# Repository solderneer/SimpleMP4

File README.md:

# SimpleMP4
A custom MP4 player designed based on the Rockwell RK2608 dedicated IC.

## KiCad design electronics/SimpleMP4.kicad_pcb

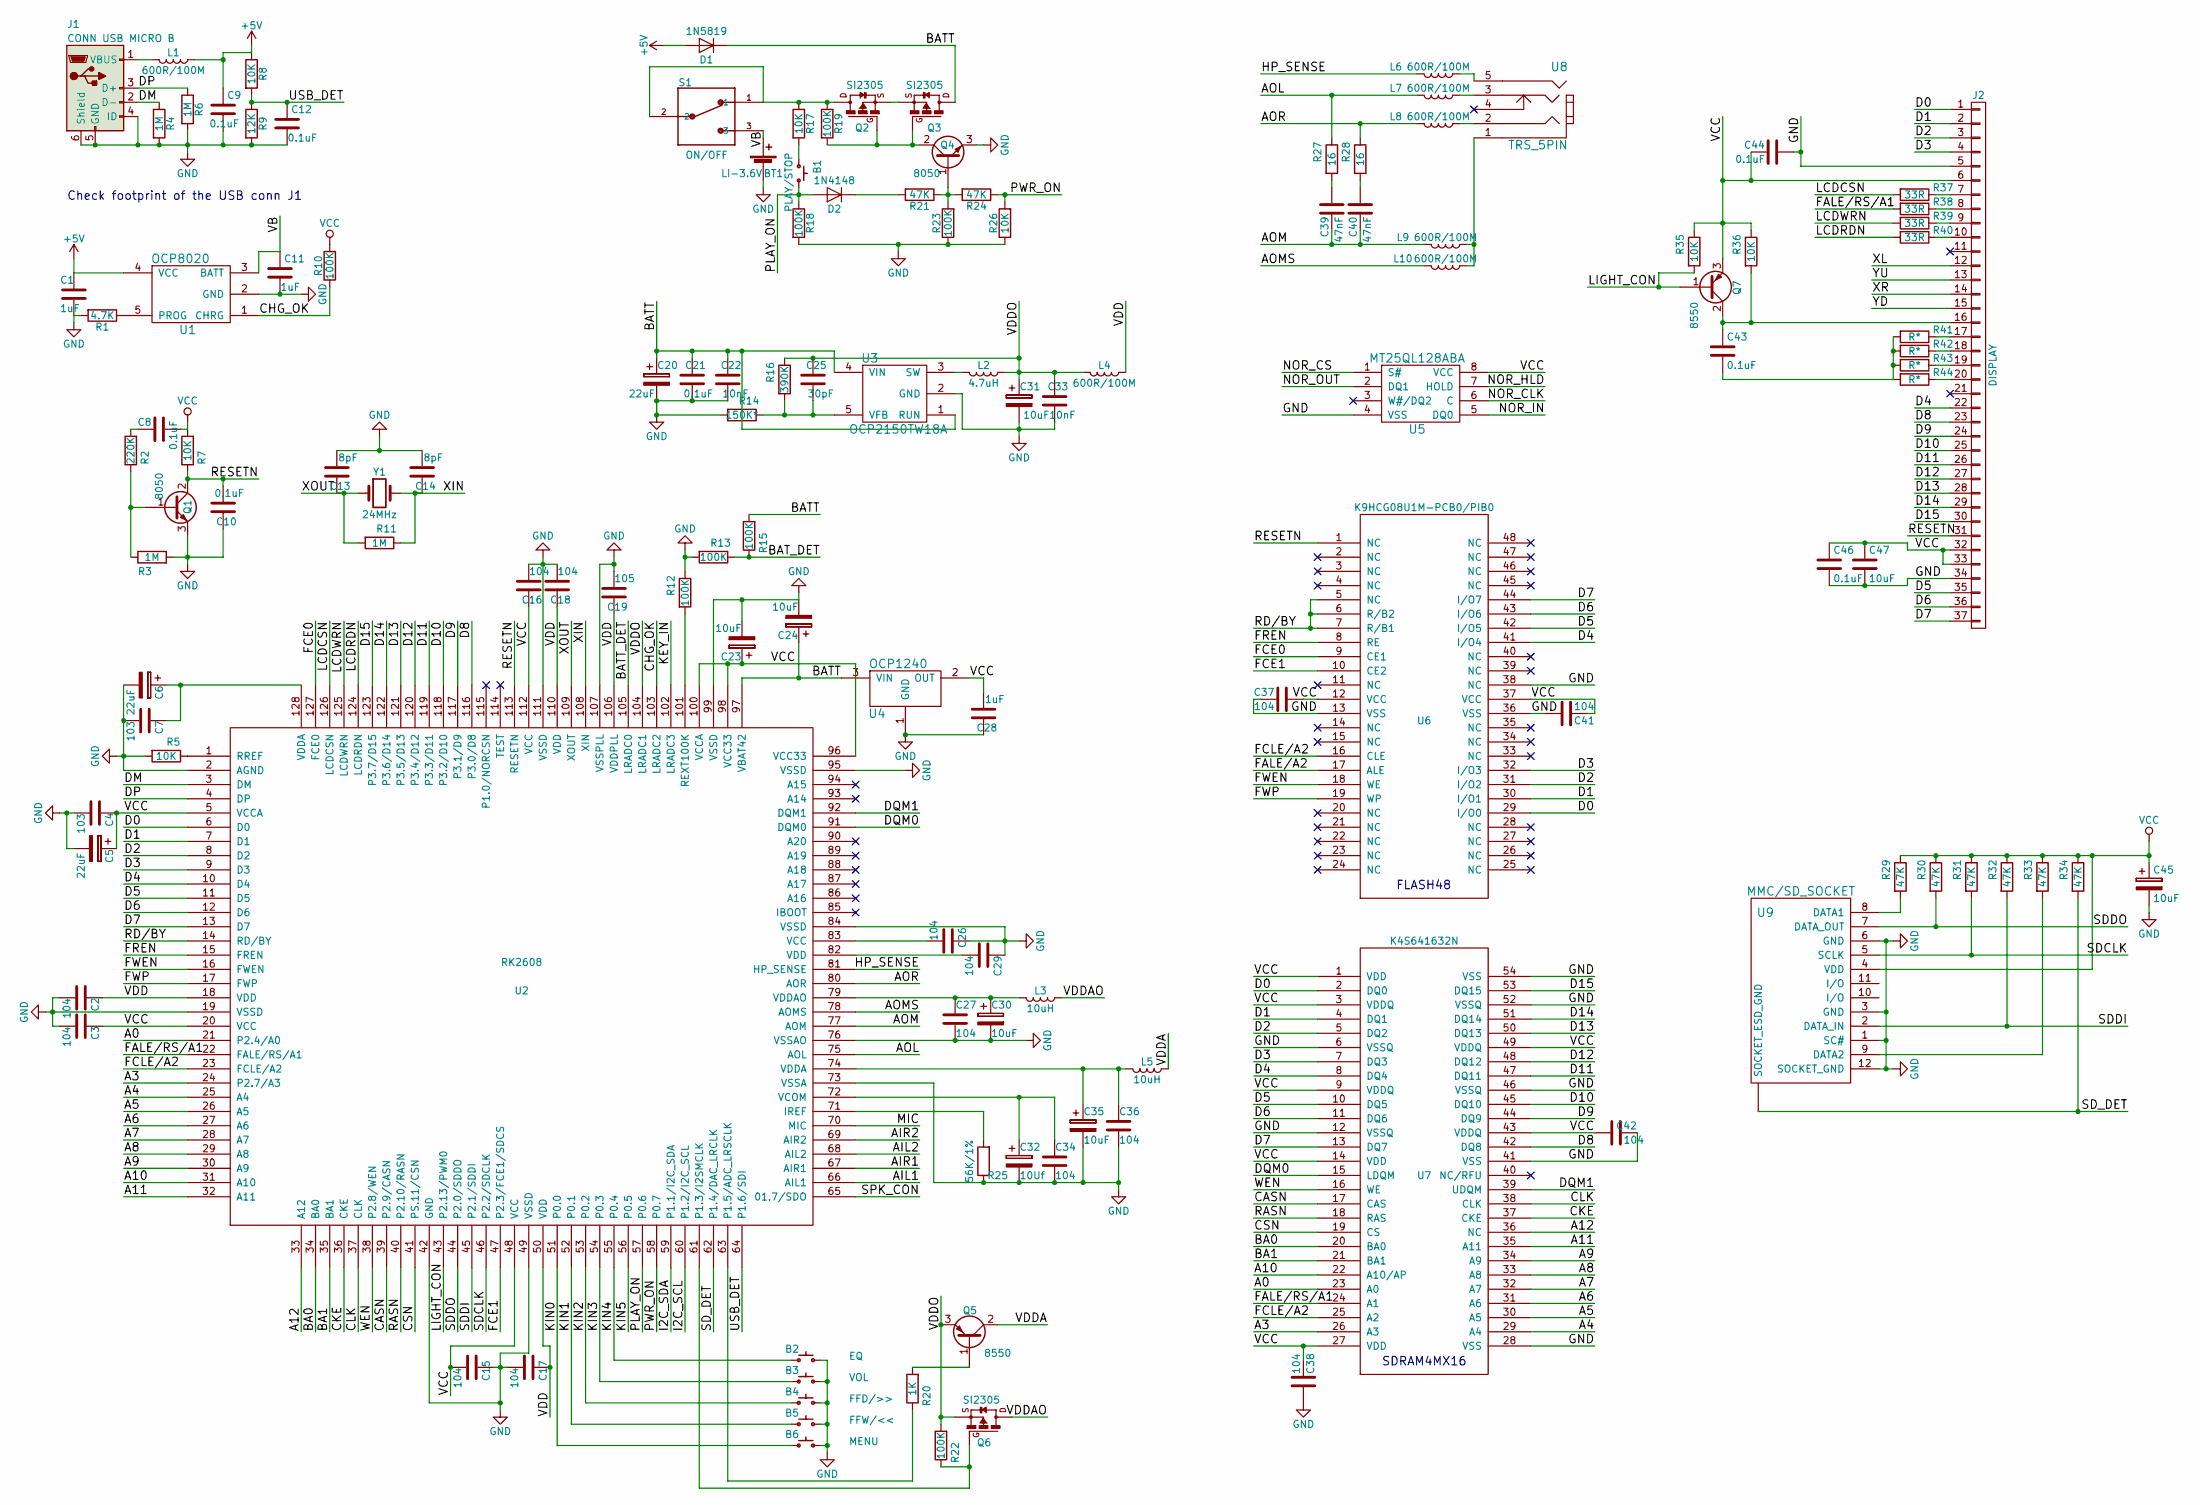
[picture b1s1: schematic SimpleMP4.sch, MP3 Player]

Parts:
B1: PLAY/STOP; SW_HP0315AFKP4-R
B2: EQ; SW_HP0315AFKP4-R
B3: VOL; SW_HP0315AFKP4-R
B4: FFD/>>; SW_HP0315AFKP4-R
B5: FFW/<<; SW_HP0315AFKP4-R
B6: MENU; SW_HP0315AFKP4-R
BT1: LI-3.6V; JST_PH_B2B-PH-SM4-TB_02x2.00mm_Straight
C1, C11: 1uF; C_0603; Digikey 399-3118-1-ND
C2, C3, C15, C16, C17, C18, C26, C27, C29, C34, C36, C37, C38, C41, C42: 104; C_0603
C4, C7: 103; C_0603
C5, C6: 22uF; CP_Elec_4x4.5
C8, C9, C10, C12, C21, C43, C44, C46: 0.1uF; C_0603; Digikey 399-1095-1-ND
C13, C14: 8pF; C_0603; Digikey 1276-1817-1-ND
C19: 105; C_0603
C20: 22uF; CP_Elec_4x4.5; Digikey PCE3857CT-ND
C22, C33: 10nF; C_0603; Digikey 478-1227-1-ND
C23, C24, C30, C35: 10uF; CP_Elec_4x4.5
C25: 30pF; C_0603; Digikey 1276-1021-1-ND
C28: 1uF; C_0603
C31, C45: 10uF; CP_Elec_4x4.5; Digikey PCE3878CT-ND
C32: 10Uf; CP_Elec_4x4.5
C39, C40: 47nF; C_0603; Digikey 399-9096-1-ND
C47: 10uF; C_0603
D1: 1N5819; D_SOD-123; Digikeyy 1N5819HW-FDICT-ND
D2: 1N4148; D_SOD-123; Digikey 1N4148W-FDIDKR-ND
J1: CONN USB MICRO B; USB_Mini-B; Digikey 609-4613-2-ND
J2: DISPLAY; KD024B
L1, L4, L6, L7, L8, L9, L10: 600R/100M; L_0603; Digikey 490-14398-2-ND
L2: 4.7uH; CR43NP-4R7MC; Digikey 308-1527-1-ND
L3, L5: 10uH; L_1210
Q1, Q4: 8050; SOT-23; Digikey MMSS8050-H-TPMSCT-ND
Q2, Q3, Q6: SI2305; SOT-23
Q5, Q7: 8550; SOT-23
R1: 4.7K; R_0603
R2: 220K; R_0603; Digikey RR08P220KDCT-ND
R3, R4, R6, R11: 1M; R_0603; Digikey A119955TR-ND
R5: 10K; R_0603
R7, R8, R17, R26, R35, R36: 10K; R_0603; Digikey 311-10KDCT-ND
R9: 12K; R_0603; Digikey P12KDBCT-ND
R10, R18, R19, R23: 100K; R_0603; Digikey RR08P100KDCT-ND
R12, R13, R15, R22: 100K; R_0603
R14: 150K*; R_0603; Digikey P150KDBCT-ND
R16: 390K; R_0603; Digikey A119962CT-ND
R20: 1K; R_0603
R21, R24, R29, R30, R31, R32, R33, R34: 47K; R_0603; Digikey P47KDBCT-ND
R25: 56K/1%; R_0603
R27, R28: 16; R_0603; Digikey A103049TR-ND
R37, R38, R39, R40: 33R; R_0603; Digikey MCT0603-33.0-CFCT-ND
R41, R42, R43, R44: R*; R_0603
S1: ON/OFF; SW_SS312SAH4-R
U1: OCP8020; SOT-23-5
U2: RK2608; LQFP-128_14x14mm_Pitch0.4mm
U3: OCP2150TW18A; SOT-23-5
U4: OCP1240; SOT-23
U5: MT25QL128ABA; SOP-8
U6: K9HCG08U1M-PCB0/PIB0; TSOP-I-48_18.4x12mm_Pitch0.5mm
U7: K4S641632N; TSOP-54
U8: TRS_5PIN; Stereo_Jack_3.5mm_Switch_Ledino_KB3SPRS
U9: MMC/SD_SOCKET; SD_Card_Receptacle
Y1: 24MHz; Crystal_SMD_HC49-SD; Digikey 535-10233-1-ND

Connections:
+5V: C1.1, C9.1, D1.2 (A), L1.1, R8.1, U1.4 (VCC)
/A0: U2.21 (P2.4/A0), U7.23 (A0)
/A3: U2.24 (P2.7/A3), U7.26 (A3)
/A4: U2.25 (A4), U7.29 (A4)
/A5: U2.26 (A5), U7.30 (A5)
/A6: U2.27 (A6), U7.31 (A6)
/A7: U2.28 (A7), U7.32 (A7)
/A8: U2.29 (A8), U7.33 (A8)
/A9: U2.30 (A9), U7.34 (A9)
/A10: U2.31 (A10), U7.22 (A10/AP)
/A11: U2.32 (A11), U7.35 (A11)
/A12: U2.33 (A12), U7.36 (NC)
/AIL1: U2.66 (AIL1)
/AIL2: U2.68 (AIL2)
/AIR1: U2.67 (AIR1)
/AIR2: U2.69 (AIR2)
/AOL: L7.2, R27.1, U2.75 (AOL)
/AOM: C39.1, C40.1, L9.2, U2.77 (AOM)
/AOMS: L10.2, U2.78 (AOMS)
/AOR: L8.2, R28.1, U2.80 (AOR)
/BA0: U2.34 (BA0), U7.20 (BA0)
/BA1: U2.35 (BA1), U7.21 (BA1)
/BATT: C20.1, C21.2, C22.2, C24.1, D1.1 (K), Q3.3 (D), R15.2, U2.97 (VBAT42), U3.1 (RUN), U3.4 (VIN), U4.3 (VIN)
/BATT_DET: U2.105 (LRADC0)
/BAT_DET: R13.1, R15.1
/CASN: U2.39 (P2.9/CASN), U7.17 (CAS)
/CHG_OK: R10.1, U1.1 (CHRG), U2.103 (LRADC2)
/CKE: U2.36 (CKE), U7.37 (CKE)
/CLK: U2.37 (CLK), U7.38 (CLK)
/CSN: U2.41 (PS.11/CSN), U7.19 (CS)
/D0: J2.1, U2.6 (D0), U6.29 (I/O0), U7.2 (DQ0)
/D1: J2.2, U2.7 (D1), U6.30 (I/O1), U7.4 (DQ1)
/D2: J2.3, U2.8 (D2), U6.31 (I/O2), U7.5 (DQ2)
/D3: J2.4, U2.9 (D3), U6.32 (I/O3), U7.7 (DQ3)
/D4: J2.22, U2.10 (D4), U6.41 (I/O4), U7.8 (DQ4)
/D5: J2.35, U2.11 (D5), U6.42 (I/O5), U7.10 (DQ5)
/D6: J2.36, U2.12 (D6), U6.43 (I/O6), U7.11 (DQ6)
/D7: J2.37, U2.13 (D7), U6.44 (I/O7), U7.13 (DQ7)
/D8: J2.23, U2.116 (P3.0/D8), U7.42 (DQ8)
/D9: J2.24, U2.117 (P3.1/D9), U7.44 (DQ9)
/D10: J2.25, U2.118 (P3.2/D10), U7.45 (DQ10)
/D11: J2.26, U2.119 (P3.3/D11), U7.47 (DQ11)
/D12: J2.27, U2.120 (P3.4/D12), U7.48 (DQ12)
/D13: J2.28, U2.121 (P3.5/D13), U7.50 (DQ13)
/D14: J2.29, U2.122 (P3.6/D14), U7.51 (DQ14)
/D15: J2.30, U2.123 (P3.7/D15), U7.53 (DQ15)
/DM: J1.2 (D-), R4.1, U2.3 (DM)
/DP: J1.3 (D+), R6.1, U2.4 (DP)
/DQM0: U2.91 (DQM0), U7.15 (LDQM)
/DQM1: U2.92 (DQM1), U7.39 (UDQM)
/FALE/A2: U6.17 (ALE)
/FALE/RS/A1: R38.2, U2.22 (FALE/RS/A1), U7.24 (A1)
/FCE0: U2.127 (FCE0), U6.9 (CE1)
/FCE1: U2.47 (P2.3/FCE1/SDCS), U6.10 (CE2)
/FCLE/A2: U2.23 (FCLE/A2), U6.16 (CLE), U7.25 (A2)
/FREN: U2.15 (FREN), U6.8 (RE)
/FWEN: U2.16 (FWEN), U6.18 (WE)
/FWP: U2.17 (FWP), U6.19 (WP)
/HP_SENSE: L6.2, U2.81 (HP_SENSE)
/I2C_SCL: U2.60 (P1.2/I2C_SCL)
/I2C_SDA: U2.59 (P1.1/I2C_SDA)
/KEY_IN: U2.102 (LRADC3)
/KIN0: B6.1, U2.51 (P0.0)
/KIN1: B5.1, U2.52 (P0.1)
/KIN2: B4.1, U2.53 (P0.2)
/KIN3: B3.1, U2.54 (P0.3)
/KIN4: B2.1, U2.55 (P0.4)
/KIN5: U2.56 (P0.5)
/LCDCSN: R37.2, U2.126 (LCDCSN)
/LCDRDN: R40.2, U2.124 (LCDRDN)
/LCDWRN: R39.2, U2.125 (LCDWRN)
/LIGHT_CON: Q7.1 (B), R35.2, U2.43 (P2.13/PWM0)
/MIC: U2.70 (MIC)
/NOR_CLK: U5.6 (C)
/NOR_CS: U5.1 (S#)
/NOR_HLD: U5.7 (HOLD)
/NOR_IN: U5.5 (DQ0)
/NOR_OUT: U5.2 (DQ1)
/PLAY_ON: B1.2, D2.2 (A), R18.1, U2.57 (P0.6)
/PWR_ON: R24.1, R26.2, U2.58 (P0.7)
/RASN: U2.40 (P2.10/RASN), U7.18 (RAS)
/RD/BY: U2.14 (RD/BY), U6.5 (NC), U6.6 (R/B2), U6.7 (R/B1)
/RESETN: C10.2, J2.31, Q1.2 (C), R7.1, U2.113 (RESETN), U6.1 (NC)
/SDCLK: R31.2, U2.46 (P2.2/SDCLK), U9.5 (SCLK)
/SDDI: R32.2, U2.45 (P2.1/SDDI), U9.2 (DATA_IN)
/SDDO: R30.2, U2.44 (P2.0/SDDO), U9.7 (DATA_OUT)
/SD_DET: R34.2, U2.62 (P1.4/DAC_LRCLK), U9.~ (SOCKET_ESD_GND)
/SPK_CON: U2.65 (01.7/SDO)
/USB_DET: C12.1, R8.2, R9.1, U2.64 (P1.6/SDI)
/VB: BT1.1 (+), C11.1, S1.3, U1.3 (BATT)
/VDD: C2.2, C17.2, C18.1, C19.1, L4.1, U2.18 (VDD), U2.50 (VDD), U2.106 (VDDPLL), U2.110 (VDD)
/VDDA: L5.1, Q5.2 (C)
/VDDAO: L3.1, Q6.3 (D)
/VDDO: C25.2, C31.1, C33.2, L2.1, L4.2, Q5.3 (E), Q6.2 (S), R16.1, R22.2, U2.104 (LRADC1)
/WEN: U2.38 (P2.8/WEN), U7.16 (WE)
/XIN: C14.1, R11.1, U2.108 (XIN), Y1.2
/XL: J2.12
/XOUT: C13.1, R11.2, U2.109 (XOUT), Y1.1
/XR: J2.14
/YD: J2.15
/YU: J2.13
GND: B2.2, B3.2, B4.2, B5.2, B6.2, BT1.2 (-), C1.2, C2.1, C3.1, C4.1, C5.2, C6.2, C7.1, C9.2, C10.1, C11.2, C12.2, C13.2, C14.2, C15.2, C16.2, C17.1, C18.2, C19.2, C20.2, C21.1, C22.1, C23.2, C24.2, C26.1, C27.2, C28.1, C29.1, C30.2, C31.2, C32.2, C33.1, C34.2, C35.2, C36.2, C37.1, C38.2, C41.2, C42.2, C44.2, C45.2, C46.2, C47.2, J1.4 (ID), J1.5 (GND), J1.6 (Shield), J2.5, J2.34, Q1.3 (E), Q4.3 (E), R1.2, R3.2, R4.2, R5.2, R6.2, R9.2, R12.1, R13.2, R14.2, R18.2, R23.1, R25.1, R26.1, U1.2 (GND), U2.2 (AGND), U2.19 (VSSD), U2.42 (GND), U2.49 (VSSD), U2.73 (VSSA), U2.76 (VSSAO), U2.84 (VSSD), U2.95 (VSSD), U2.99 (VSSD), U2.107 (VSSPLL), U2.111 (VSSD), U3.2 (GND), U4.1 (GND), U5.4 (VSS), U6.13 (VSS), U6.36 (VSS), U6.38 (NC), U7.6 (VSSQ), U7.12 (VSSQ), U7.28 (VSS), U7.41 (VSS), U7.46 (VSSQ), U7.52 (VSSQ), U7.54 (VSS), U9.1 (SC#), U9.3 (GND), U9.6 (GND), U9.12 (SOCKET_GND)
unnamed: B1.1, R17.2
unnamed: C6.1, C7.2, U2.128 (VDDA)
unnamed: C8.1, R2.2
unnamed: C25.1, R14.1, R16.2, U3.5 (VFB)
unnamed: C26.2, U2.83 (VCC)
unnamed: C27.1, C30.1, L3.2, U2.79 (VDDAO)
unnamed: C29.2, U2.82 (VDD)
unnamed: C32.1, C34.1, U2.72 (VCOM)
unnamed: C35.1, C36.1, L5.2, U2.74 (VDDA)
unnamed: C39.2, R27.2
unnamed: C40.2, R28.2
unnamed: C43.1, J2.16, Q7.2 (C), R36.2
unnamed: C43.2, R41.2, R42.2, R43.2, R44.2
unnamed: D2.1 (K), R21.2
unnamed: J1.1 (VBUS), L1.2
unnamed: J2.7, R37.1
unnamed: J2.8, R38.1
unnamed: J2.9, R39.1
unnamed: J2.10, R40.1
unnamed: J2.17, R41.1
unnamed: J2.18, R42.1
unnamed: J2.19, R43.1
unnamed: J2.20, R44.1
unnamed: L2.2, U3.3 (SW)
unnamed: L6.1, U8.5
unnamed: L7.1, U8.3
unnamed: L8.1, U8.2
unnamed: L9.1, L10.1, U8.1
unnamed: Q1.1 (B), R2.1, R3.1
unnamed: Q2.1 (G), Q3.1 (G), Q4.2 (C), R19.2
unnamed: Q2.2 (S), Q3.2 (S)
unnamed: Q2.3 (D), R17.1, R19.1, S1.1, S1.2
unnamed: Q4.1 (B), R21.1, R23.2, R24.2
unnamed: Q5.1 (B), R20.2
unnamed: Q6.1 (G), R22.1, U2.61 (P1.3/I2SMCLK)
unnamed: R1.1, U1.5 (PROG)
unnamed: R5.1, U2.1 (RREF)
unnamed: R12.2, U2.101 (REXT100K)
unnamed: R20.1, U2.63 (P1.5/ADC_LRSCLK)
unnamed: R25.2, U2.71 (IREF)
unnamed: R29.2, U9.8 (DATA1)
unnamed: R33.2, U9.9 (DATA2)
VCC: C3.2, C4.2, C5.1, C8.2, C15.1, C16.1, C23.1, C28.2, C37.2, C38.1, C41.1, C42.1, C44.1, C45.1, C46.1, C47.1, J2.6, J2.32, J2.33, Q7.3 (E), R7.2, R10.2, R29.1, R30.1, R31.1, R32.1, R33.1, R34.1, R35.1, R36.1, U2.5 (VCCA), U2.20 (VCC), U2.48 (VCC), U2.96 (VCC33), U2.98 (VCC33), U2.100 (VCCA), U2.112 (VCC), U4.2 (OUT), U5.8 (VCC), U6.12 (VCC), U6.37 (VCC), U7.1 (VDD), U7.3 (VDDQ), U7.9 (VDDQ), U7.14 (VDD), U7.27 (VDD), U7.43 (VDDQ), U7.49 (VDDQ), U9.4 (VDD)

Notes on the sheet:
Check footprint of the USB conn J1
FLASH48
SDRAM4MX16

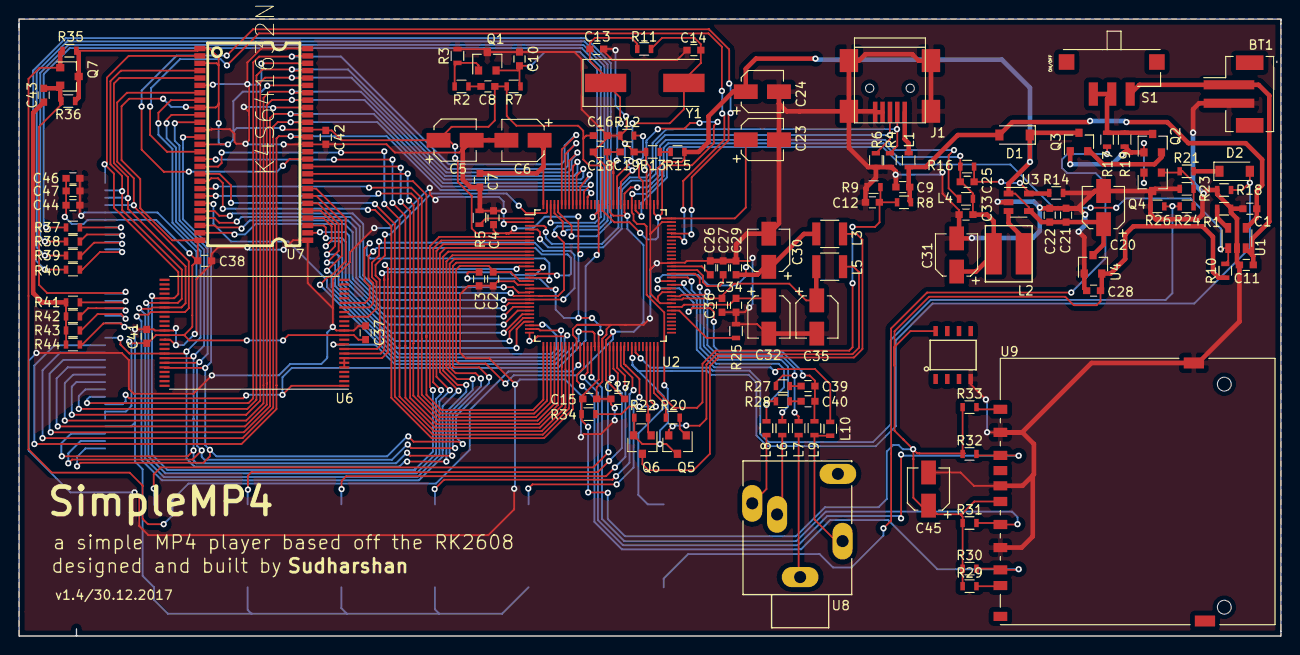
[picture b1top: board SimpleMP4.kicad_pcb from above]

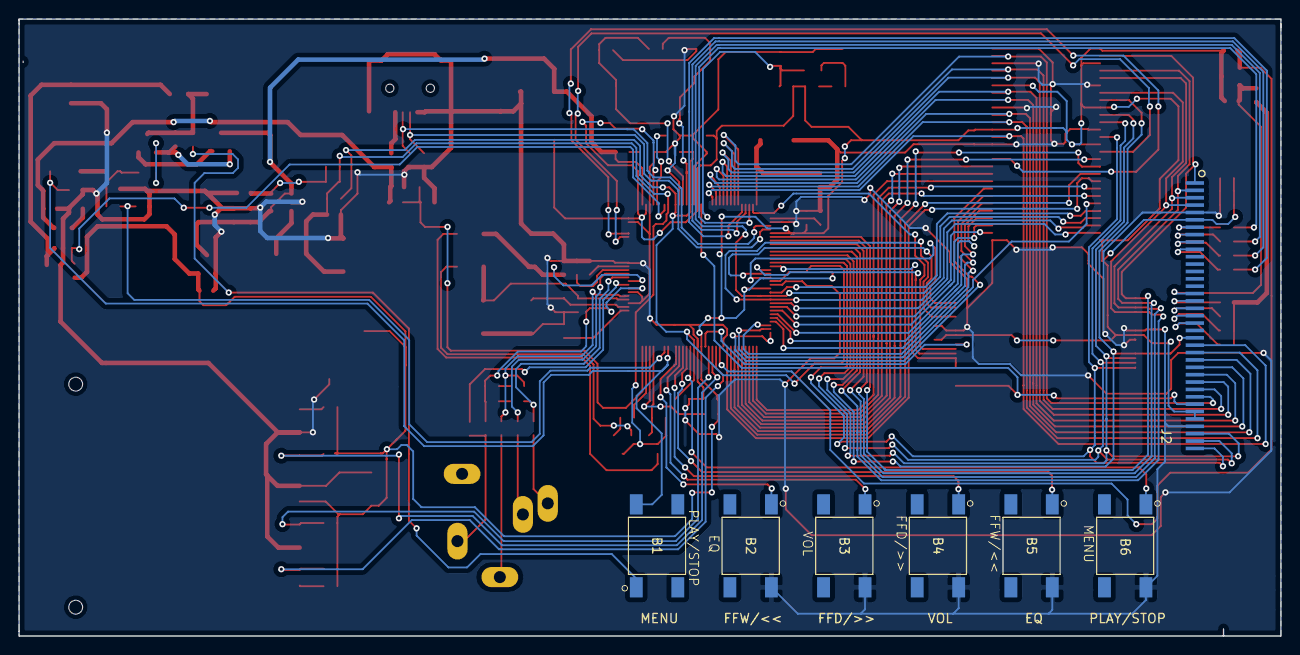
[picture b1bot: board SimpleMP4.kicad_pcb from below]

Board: 2 copper layers, 136.9 x 66.9 mm, 130 parts (7 on the bottom side), 124 nets.

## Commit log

2017-11-22 pulling pre existing firmware and docs
2017-12-10 added datasheets
2017-12-11 added NOR32 flash datasheet
2017-12-12 added kicad project
2017-12-12 added USB section
2017-12-12 added power processing section
2017-12-12 added FM section and spk amp section
2017-12-13 added SD card section
2017-12-13 added ocp21050 section
2017-12-13 added display header
2017-12-14 added SDRAM and FLASH datasheets
2017-12-15 added flash section
2017-12-15 added SDRAM
2017-12-15 fixed some errors
2017-12-15 added RK2608
2017-12-15 finished RK2608 section
2017-12-15 added batt to poower processing circuitry
2017-12-17 updated datasheets
2017-12-17 added annotations to components
2017-12-18 added proper display and LCD backlight driver
2017-12-18 added custom TRS 5pin audio jack
2017-12-18 added TRS 5pin audio jack section
2017-12-18 added NOR Flash chip
2017-12-18 added pdf
2017-12-18 added annotations and bom
2017-12-18 cleaning up schematic
2017-12-18 added proper BOM for client
2017-12-20 fixed error in schematics
2017-12-20 compiled all used libraries
2017-12-21 added new NAND flash datasheet
2017-12-22 added netlist
2017-12-22 finalizing part values
2017-12-22 added new datasheets and organized directories
2017-12-22 updated schematics
2017-12-22 added footprints
2017-12-23 placing components around RK2608
2017-12-23 placed most components around rk2608
2017-12-23 fixed minor error in schematic'
2017-12-24 placed USB section
2017-12-24 grouped a few more components
2017-12-24 added display connector
2017-12-25 updated SOP8 footprint
2017-12-25 placed more components and defined board edge
2017-12-25 pausing for now
2017-12-25 added inductor footprints and starting to route
2017-12-25 that's it for today
2017-12-25 added partial routing
2017-12-26 routed most major parallel buses
2017-12-28 cleaned up power section
2017-12-28 added spst tactile switch footprint
2017-12-28 added test points
2017-12-28 added another data bus
2017-12-28 routed more of it
2017-12-28 routed more of the segments
2017-12-28 added routing to buttons
2017-12-29 94 unconnected left
2017-12-29 routed more connections
2017-12-29 routed headphone jack
2017-12-29 routed most connections
2017-12-29 done routing
2017-12-29 added filled zones
2017-12-29 proper silkscreen
2017-12-29 added back filled zones
2017-12-30 generated gerber files
2017-12-30 creating footprints.pretty to hold used footprints
2017-12-30 changed fp-lib-table to match new footprint locations
2017-12-30 added OSHpark renders
2017-12-30 moved silkscreen
2017-12-30 moved silkscreen of battery conn and switch
2018-01-03 added new gerber files
2018-01-03 labelling components with digikey part number
2018-01-05 SimpleMP4
2018-01-05 updating versioning details on PCB
2018-01-08 changed out FLASH chip
2018-01-08 added BOM to repo
2018-01-09 added condensed BOM
2018-01-09 added BOM folder
2018-01-09 added bom files
2023-07-01 Update README.md for posterity
